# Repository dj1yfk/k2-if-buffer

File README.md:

# Elecraft K2 IF Buffer Amplifier 

This is a reproduction of the Clifton Laboratories Z10000-K2 Buffer Amplifier,
designed by Jack R. Smith, K8ZOA (SK). The amplifier is also commercially
available from [DX Engineering](https://www.dxengineering.com/parts/dxe-z10000k2-kit#overview).

The amplifier allows to tap the K2's 4.915 MHz IF and feed it into a SDR to
realize a band scope feature.

This project contains the full KiCad design data (schmematics, PCB) and will be
extended with additional information on building and integrating this amplifier
into the K2 eventually (work in progress).

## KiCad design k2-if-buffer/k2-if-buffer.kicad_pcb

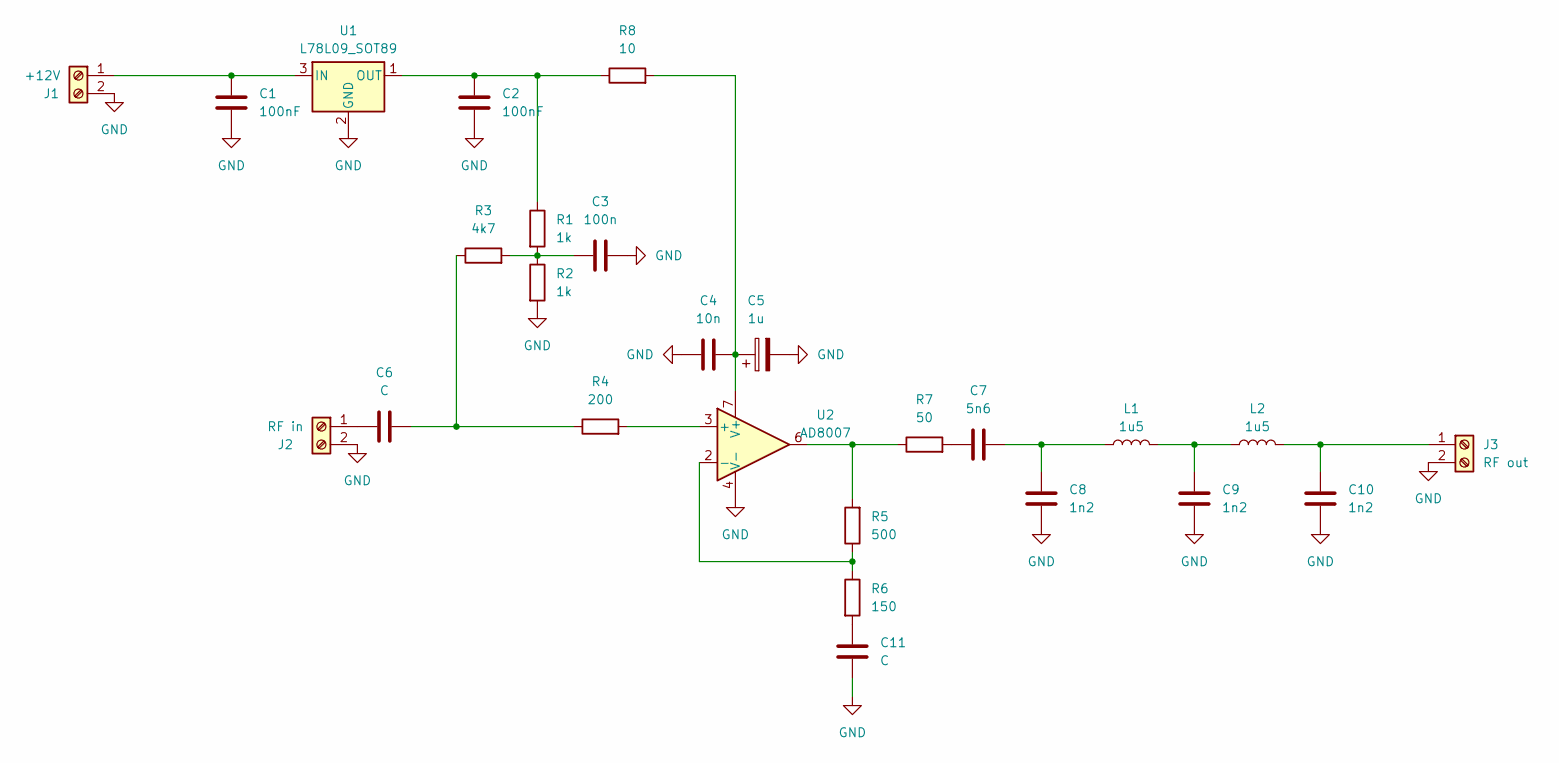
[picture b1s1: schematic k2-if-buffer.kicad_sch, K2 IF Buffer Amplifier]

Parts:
C1, C2: 100nF; C_0603_1608Metric_Pad1.08x0.95mm_HandSolder
C3: 100n; C_0603_1608Metric_Pad1.08x0.95mm_HandSolder
C4: 10n; C_0603_1608Metric_Pad1.08x0.95mm_HandSolder
C5: 1u; C_0805_2012Metric_Pad1.18x1.45mm_HandSolder
C6, C11: C; C_0603_1608Metric_Pad1.08x0.95mm_HandSolder
C7: 5n6; C_0603_1608Metric_Pad1.08x0.95mm_HandSolder
C8, C9, C10: 1n2; C_0603_1608Metric_Pad1.08x0.95mm_HandSolder
J1: +12V; Wuerth_WR-WTB_64800211622_1x02_P1.50mm_Vertical
J2: RF in; Wuerth_WR-WTB_64800211622_1x02_P1.50mm_Vertical
J3: RF out; Wuerth_WR-WTB_64800211622_1x02_P1.50mm_Vertical
L1, L2: 1u5; L_0805_2012Metric_Pad1.05x1.20mm_HandSolder
R1, R2: 1k; R_0603_1608Metric_Pad0.98x0.95mm_HandSolder
R3: 4k7; R_0603_1608Metric_Pad0.98x0.95mm_HandSolder
R4: 200; R_0603_1608Metric_Pad0.98x0.95mm_HandSolder
R5: 500; R_0603_1608Metric_Pad0.98x0.95mm_HandSolder
R6: 150; R_0603_1608Metric_Pad0.98x0.95mm_HandSolder
R7: 50; R_0603_1608Metric_Pad0.98x0.95mm_HandSolder
R8: 10; R_0603_1608Metric_Pad0.98x0.95mm_HandSolder
U1: L78L09_SOT89; SOT-89-3
U2: AD8007; SOIC-8_3.9x4.9mm_P1.27mm

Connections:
GND: C1.2, C2.2, C3.2, C4.1, C5.2, C8.1, C9.1, C10.1, C11.1, J1.2, J2.2, J3.2, R2.2, U1.2 (GND), U2.4 (V-)
unnamed: C3.1, R1.2, R2.1, R3.2
unnamed: C6.2, R3.1, R4.1
unnamed: C7.1, R7.2
unnamed: C7.2, C8.2, L1.1
unnamed: C9.2, L1.2, L2.1
unnamed: C11.2, R6.2
unnamed: C1.1, J1.1, U1.3 (IN)
unnamed: C6.1, J2.1
unnamed: C10.2, J3.1, L2.2
unnamed: R5.2, R7.1, U2.6
unnamed: C2.1, R1.1, R8.1, U1.1 (OUT)
unnamed: R4.2, U2.3 (+)
unnamed: R5.1, R6.1, U2.2 (-)
unnamed: C4.2, C5.1, R8.2, U2.7 (V+)

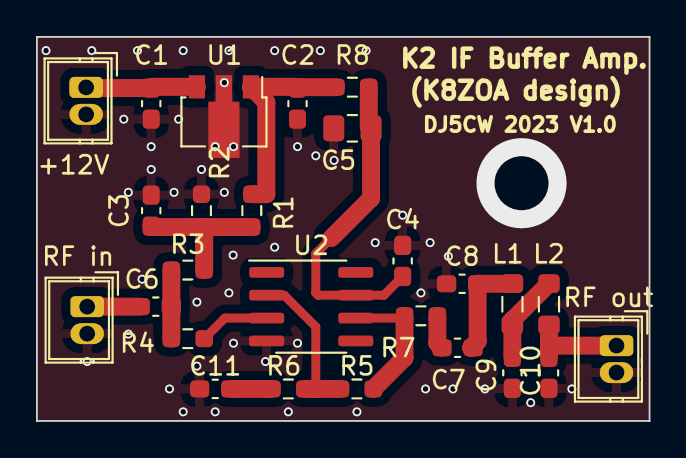
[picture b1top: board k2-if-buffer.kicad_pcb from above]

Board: 2 copper layers, 34.0 x 21.3 mm, 26 parts (0 on the bottom side), 15 nets.

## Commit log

2023-11-17 Finish schematic, associate footprints.
2023-11-17 Draft PCB (some footprints pending)
